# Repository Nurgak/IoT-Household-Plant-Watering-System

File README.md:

# IoT Household Plant Watering System

This project is about building an internet connected switch and use it together with a water pump to automatically irrigate household plants.

It is meant to be part of a larger home automation network, where nodes are controlled from a central hub via a [Node-RED](https://nodered.org/) server, it can also be used as stand-alone.

The [build process](https://hackaday.io/project/27108-iot-household-plant-watering-system) is documented on Hackaday.io.

## Hardware

The [complete bill-of-materials](https://hackaday.io/project/27108-iot-household-plant-watering-system) is documented on Hackaday.io. The electronic files, including schematic and layout, are under `/hardware`.

The diaphragm pump is off of eBay and can function between 6-12V.

## Software

The software is developed with [Arduino IDE](https://www.arduino.cc/en/Main/Software) and the [ESP8266 core](https://github.com/esp8266/Arduino). The MQTT libraries are courtesy of [knolleary](https://github.com/knolleary/pubsubclient).

Before uploading the code the network credentials, MQTT broker address and port and the topic names need to be set. Once configured and uploaded the software can be [updated over WiFi](http://esp8266.github.io/Arduino/versions/2.0.0/doc/ota_updates/ota_updates.html) (Over-The-Air updating) from Arduino IDE.

## Usage

The system is controlled via [MQTT messages](https://en.wikipedia.org/wiki/MQTT), the suggested approach is to use [Node-RED](https://nodered.org/) server with an MQTT broker to configure the control flow.

The device subscribes to the following MQTT messages:

* **water**: sets the state of the pump, 1 activates and 0 deactivates it
* **timeout**: sets the maximum time the pump is allowed to function in milliseconds, if the pump is not stopped before the timeout runs out it will stop automatically
* **dutycycle**: sets the PWM duty cycle from 0 to 100% for the motor, allows to control the speed of the pump

The settings for the timeout and duty cycle are stored in the EEPROM and persist over reboots.

## License

The software is licensed under [GNU General Public License](https://en.wikipedia.org/wiki/GNU_General_Public_License).

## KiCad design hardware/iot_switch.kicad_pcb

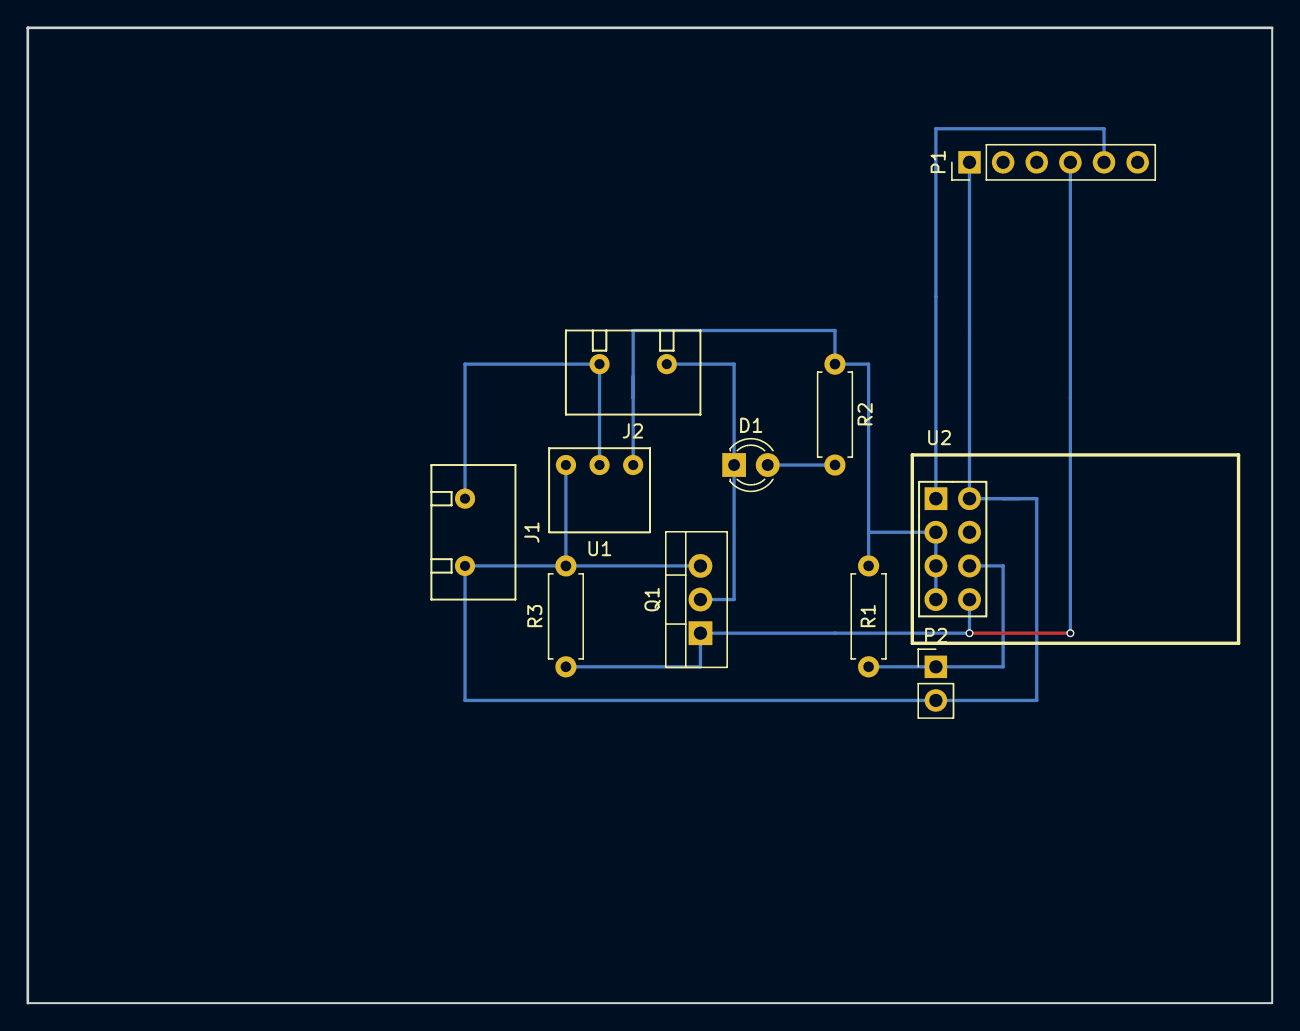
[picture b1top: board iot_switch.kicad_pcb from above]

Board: 2 copper layers, 94.0 x 73.7 mm, 11 parts (0 on the bottom side), 8 nets.

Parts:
D1: LED; LED_D3.0mm
J1: 6-20V in; Screw_terminal
J2: Load; Screw_terminal
P1: PROG; Pin_Header_Straight_1x06_Pitch2.54mm
P2: PROG_JP; Pin_Header_Straight_1x02_Pitch2.54mm
Q1: IRL2703; TO-220_Vertical
R1, R2, R3: 1k; R_Axial_DIN0207_L6.3mm_D2.5mm_P7.62mm_Horizontal
U1: AP1117-33; 1117
U2: ESP8266-01; ESP-01

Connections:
+3V3: R1.1, R2.1, U1.2, U2.3, U2.5, U2.7
GND: J1.2, P1.1, P2.2, Q1.3, R3.2, U1.1, U2.2
unnamed: D1.1, J2.1, Q1.2
unnamed: D1.2, R2.2
unnamed: P2.1, R1.2, U2.6
RX: P1.4, Q1.1, R3.1, U2.8
TX: P1.5, U2.1
VDD: J1.1, J2.2, U1.3
